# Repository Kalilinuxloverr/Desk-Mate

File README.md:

# Desk-Mate

Ein kleiner Wall-E-artiger Schreibtisch-Begleiter: eine Ampel für alles, was dich braucht (Claude Code, Browser-Downloads, Steam), ein Deck mit Motorfadern und Soft-Keys, ein Kopf mit zwei Augen-Displays. Verbunden per USB, BLE und WiFi; steuerbar vom Mac, vom Handy und über das Haus-MQTT. Alles Through-Hole, alles 3D-gedruckt, alles dokumentiert — inklusive Arbeitszeit.

**Zwischenstand (2026-10-09):**

| Schritt | Stand |
|---|---|
| Design-Spec (18 Grill-Fragen) | ✅ [`docs/superpowers/specs/`](docs/superpowers/specs/2026-08-22-desk-mate-design.md) |
| Pin-Map gegen Datenblatt + DevKit-Schaltplan verifiziert | ✅ [`firmware/arduino/deskmate/pins.h`](firmware/arduino/deskmate/pins.h) |
| Stückliste mit Quellen und Preisen, Teile bestellt (Amazon ~142 €) | ✅ [`hardware/bom.md`](hardware/bom.md) |
| KiCad final: Mainboard 100×100 · Frontpanel 120×136 · Augen-Adapter 42×30 — nur THT, Teile von Reichelt, Silkscreen mit Logo und Pin-Namen, ERC/DRC sauber, Gerber exportiert | ✅ [`hardware/kicad/`](hardware/kicad/README.md) |
| Bestellung Reichelt + JLCPCB | 🔜 bereit — Gerber in `hardware/kicad/<board>/fab/`, Liste in [`vault/Bestellungen/2026-10-09-reichelt.md`](vault/Bestellungen/2026-10-09-reichelt.md) |
| Firmware · Agent/App · Gehäuse | ⬜ danach |

Arbeitszeit und Tagesprotokolle: [`vault/Log/`](vault/Log/) · Projektseite: Portfolio-Eintrag P12.

```
 ┌─────────────────────┐
 │ KOPF  (pan/tilt)    │  Augen-Adapter-PCB → 2× GC9A01 (rund, 1,28")
 │                     │  WS2812-Ring (Ampel) · 2× MG90S im Hals
 ├─────────────────────┤
 │ BAUCH / DECK        │  FRONTPANEL-PCB
 │  [ 2,8" ILI9341 ]   │   6 Soft-Keys unter dem Display
 │  [k][k][k][k][k][k] │   4 Makro-Keys · EC11-Encoder
 │  |F| [k][k] (o) |F| │   2(4)× X32-Motorfader · MCP23017 · MPR121
 │  |F|  [k][k]    |F| │
 ├─────────────────────┤
 │ BASE (statisch)     │  MAINBOARD-PCB
 │  USB-C(D) USB-C(P)  │   ESP32-S3 DevKitC-1 · 2× USB-C · LD1117V33
 │  BME680             │   2(4)× DRV8833 · VM-Boost optional
 └─────────────────────┘
          │ USB / BLE / WiFi-MQTT
   ┌──────┴──────┐      ┌──────────┐      ┌────────────┐
   │ macOS-Agent │◄────►│ iOS-App  │      │ Claude Code│──Hooks──► Agent
   │ (Menüleiste)│ MQTT │          │      └────────────┘
   └─────────────┘      └──────────┘
```

| Pfad | Inhalt |
|---|---|
| `docs/superpowers/specs/` | Design-Spec (die eine Wahrheit für Hardware, Pin-Map, Protokolle) |
| `docs/superpowers/plans/` | Implementierungspläne je Phase |
| `docs/relic/` | Der Ursprungs-Prompt, unverändert |
| [`docs/anleitung/`](docs/anleitung/) | Bauanleitung (wächst mit dem Projekt) |
| `docs/logo/` | Logo (SVG) |
| `vault/` | Obsidian-Vault: Tagesblätter mit Arbeitszeit, Entscheidungen, Bestellungen |
| `hardware/kicad/` | Mainboard, Frontpanel, Augen-Adapter (KiCad 10) |
| `hardware/3d/` | Gehäuse (STEP + STL) |
| `hardware/bom.md` | Stückliste |
| `firmware/arduino/deskmate/` | ESP32-S3-Firmware (arduino-cli) |
| `app/` | macOS-Agent + iOS-App (Swift, XcodeGen) |
| `agent-windows/` | Windows-Tray (Python, Phase 2) |
| `server/` | Vercel-Function für Push |
| `tools/` | Session-Hooks, Secret-Check |

## Hardware

| Mainboard (Base) | Frontpanel (Deck) | Augen-Adapter |
|---|---|---|
|  |  |  |

Drei Through-Hole-Platinen, alle Module gesteckt (ESP32-S3-DevKitC-1, Pololu DRV8833, MPR121, Displays). Schaltpläne als PDF, STEP-Modelle und JLCPCB-Gerber-Zips liegen in `hardware/kicad/<board>/fab/`; Aufbau und Entwurfsregeln in [`hardware/kicad/README.md`](hardware/kicad/README.md), Bestellanleitung in [`docs/anleitung/01-platinen.md`](docs/anleitung/01-platinen.md).

## Bauen

Nach dem Klonen einmalig:

```bash
git config core.hooksPath tools/githooks   # Secret-Check vor jedem Commit
sh tools/test-check-secrets.sh             # muss "OK" sagen
sh tools/test-session-hooks.sh             # muss "OK" sagen
sh tools/test-pins.sh                      # Pin-Map-Regeln
sh tools/test-kicad.sh                     # ERC + DRC + Netzliste (braucht KiCad 10 unter /Applications)
```

KiCad-Dateien neu erzeugen/exportieren: siehe [`hardware/kicad/README.md`](hardware/kicad/README.md). Firmware- und App-Befehle kommen mit den jeweiligen Phasen dazu (siehe `CLAUDE.md`).

## Lizenz

MIT (Code). Lizenz für die Hardware-Dateien wird noch festgelegt.

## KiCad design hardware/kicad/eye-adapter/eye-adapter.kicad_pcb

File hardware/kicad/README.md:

# KiCad — drei Platinen, eine JLCPCB-Bestellung

| Ordner | Platine | Maß | Inhalt |
|---|---|---|---|
| `mainboard/` | Base | 100 × 100 mm | S3-DevKit-Sockel, Schraubklemme für das USB-C-Breakout (5 V/3 A), Polyfuse + SB540, LD1117V33, 2× DRV8833-Sockel, Servo/ARGB/I²C-Stiftleisten, Augen-Kabel IDC 2×5, IDC 2×15, MT3608-Header (VM-Boost, optional) |
| `frontpanel/` | Deck | 120 × 136 mm | 10× MX, EC11, MCP23017, MPR121-Stiftleiste (Modul per Kabel), ILI9341-Sockel + 4 Abstandshalter, 4× Fader-Header, Backlight-Schalter, IDC 2×15 |
| `eye-adapter/` | Kopf | 42 × 30 mm | IDC 2×5 ein, 2× 1×7-Stiftleiste für die GC9A01 (per Dupont-Kabel) |
| `lib/` | — | — | Projektbibliothek `deskmate.kicad_sym` + `deskmate.pretty` (Modul-Sockel, Polyfuse) |
| `gen/` | — | — | Generator (siehe unten) |
| `<board>/fab/` | — | — | Gerber/Drill-Zip, STEP, Render — das geht zu JLCPCB |

Regeln (JLCPCB 2-Lagen): Leiterbahn ≥ 0,2 mm, Abstand ≥ 0,127 mm, Via 0,8/0,4 mm, Rand 0,3 mm. Netzklassen (Breite / Abstand 0,13): Default 0,25, Power 1,0 (Mainboard) bzw. 0,8 (Frontpanel), Motor 0,6, Power3V3 0,6 — Werte stehen in `gen/boards.py` und `gen/build_sch.py`. Massefläche beidseitig, Sperrzone unter der DevKit-Antenne.

## Generator statt Handarbeit (Erstversion)

Die Erstversion aller Dateien wurde aus `gen/boards.py` erzeugt — eine Tabelle „Bauteil → Pin → Netz → Position“. So sind Schaltplan, Layout und `netlist.json` per Konstruktion identisch, und `tools/test-kicad.sh` prüft das gegen KiCads eigene Netzliste.

```bash
cd hardware/kicad/gen
python3 build_sch.py                       # Bibliothek, Schaltpläne, Projekte, netlist.json
KIPY=/Applications/KiCad/KiCad.app/Contents/Frameworks/Python.framework/Versions/3.9/bin/python3
$KIPY build_pcb.py mainboard --force       # Layout platzieren, Freerouting, Zonen füllen
$KIPY export_fab.py mainboard              # Gerber/Drill/STEP/Render nach mainboard/fab/
sh ../../../tools/test-kicad.sh            # ERC + DRC + Netzlisten-Abgleich
```

`build_pcb.py` routet bis zu 6-mal mit wechselnder Strategie und behält den ersten Lauf mit 0 offenen Verbindungen; GND-Pads sind vollflächig an die Massefläche angebunden (beim Löten heißer/länger). Freerouting: `~/Applications/freerouting-2.3.0.jar` (Java 17+; `curl -L -o ~/Applications/freerouting-2.3.0.jar https://github.com/freerouting/freerouting/releases/download/v2.3.0/freerouting-2.3.0.jar`).

**Wichtig:** Sobald in der KiCad-GUI etwas geändert wurde, sind die `.kicad_sch`/`.kicad_pcb` die Wahrheit — `build_*.py` nicht mehr blind laufen lassen (`build_pcb.py` weigert sich ohne `--force`). Der Generator ist ein Bootstrap, kein Roundtrip.

Der Schaltplan ist „Label-Stil“: jedes Pin trägt ein globales Label, keine Leitungen. Elektrisch vollständig, optisch schlicht — in der GUI beliebig umsortierbar.

## Was vor der Bestellung am echten Teil zu prüfen ist

Siehe `vault/Hardware/Module-Masse.md` (Quellen + Konfidenz). Kurz: DevKit-Reihenabstand 22,86 (hoch), Pololu-Raster 10,16 (hoch), MPR121-Clone 17,78 (mittel — nachmessen), ILI9341 MSP2807-Löcher (hoch), X32-Fader-Pins (unbekannt — Drähte an Stiftleiste).

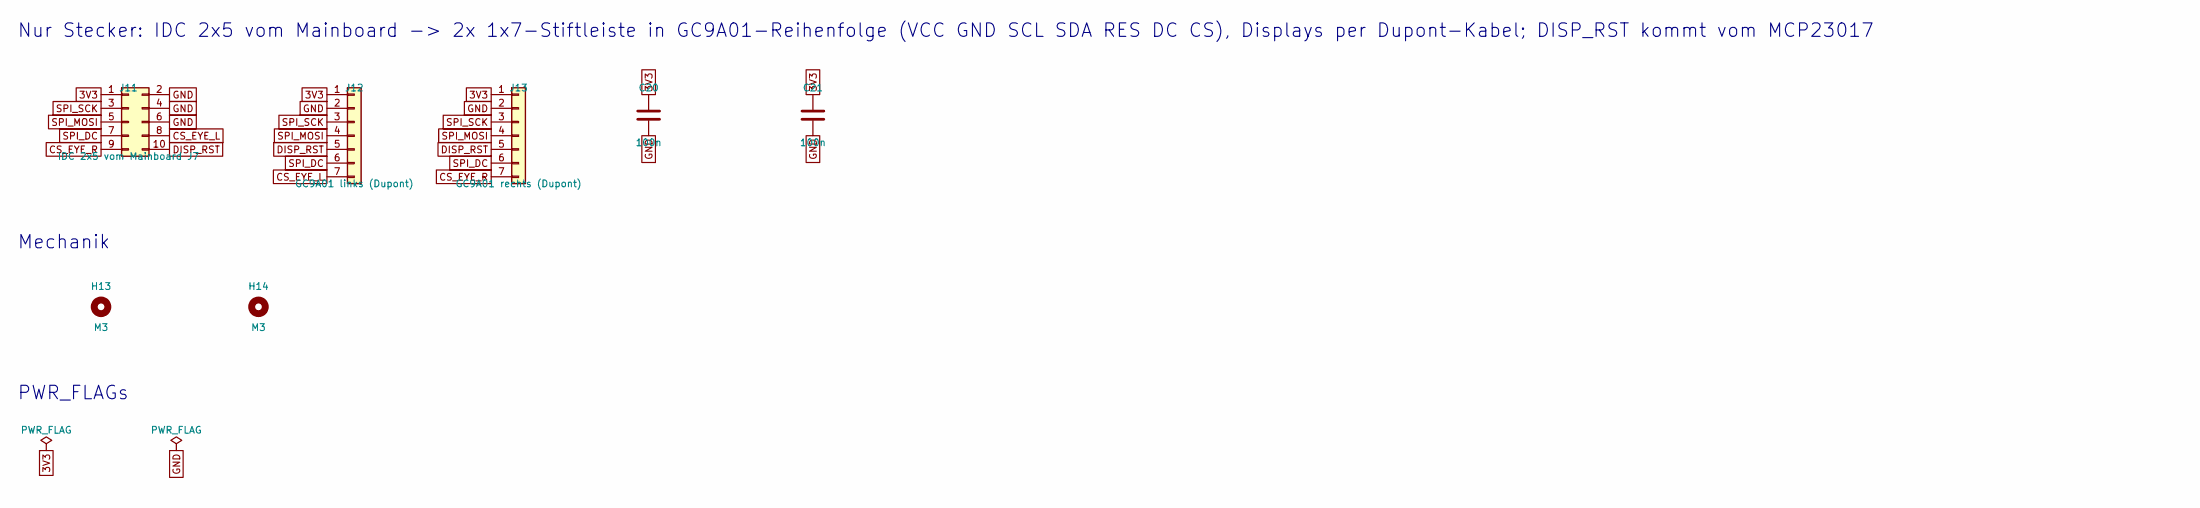
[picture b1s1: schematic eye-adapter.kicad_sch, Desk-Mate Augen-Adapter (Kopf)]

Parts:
C20, C21: 100n; C_Disc_D5.0mm_W2.5mm_P5.00mm
H13, H14: M3; MountingHole_3.2mm_M3
J11: IDC 2x5 vom Mainboard J7; IDC-Header_2x05_P2.54mm_Vertical
J12: GC9A01 links (Dupont); PinHeader_1x07_P2.54mm_Vertical
J13: GC9A01 rechts (Dupont); PinHeader_1x07_P2.54mm_Vertical

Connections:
3V3: C20.1, C21.1, J11.1, J12.1, J13.1
CS_EYE_L: J11.8, J12.7
CS_EYE_R: J11.9, J13.7
DISP_RST: J11.10, J12.5, J13.5
GND: C20.2, C21.2, J11.2, J11.4, J11.6, J12.2, J13.2
SPI_DC: J11.7, J12.6, J13.6
SPI_MOSI: J11.5, J12.4, J13.4
SPI_SCK: J11.3, J12.3, J13.3

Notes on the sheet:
Nur Stecker: IDC 2x5 vom Mainboard -> 2x 1x7-Stiftleiste in GC9A01-Reihenfolge (VCC GND SCL SDA RES DC CS), Displays per Dupont-Kabel; DISP_RST kommt vom MCP23017
Mechanik
PWR_FLAGs

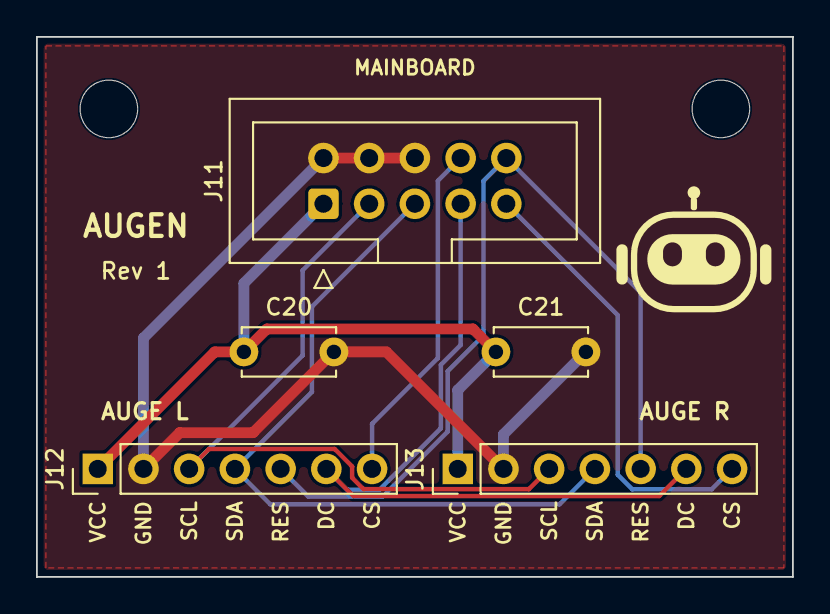
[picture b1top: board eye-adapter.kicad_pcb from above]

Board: 2 copper layers, 42.0 x 30.0 mm, 7 parts (0 on the bottom side), 8 nets.

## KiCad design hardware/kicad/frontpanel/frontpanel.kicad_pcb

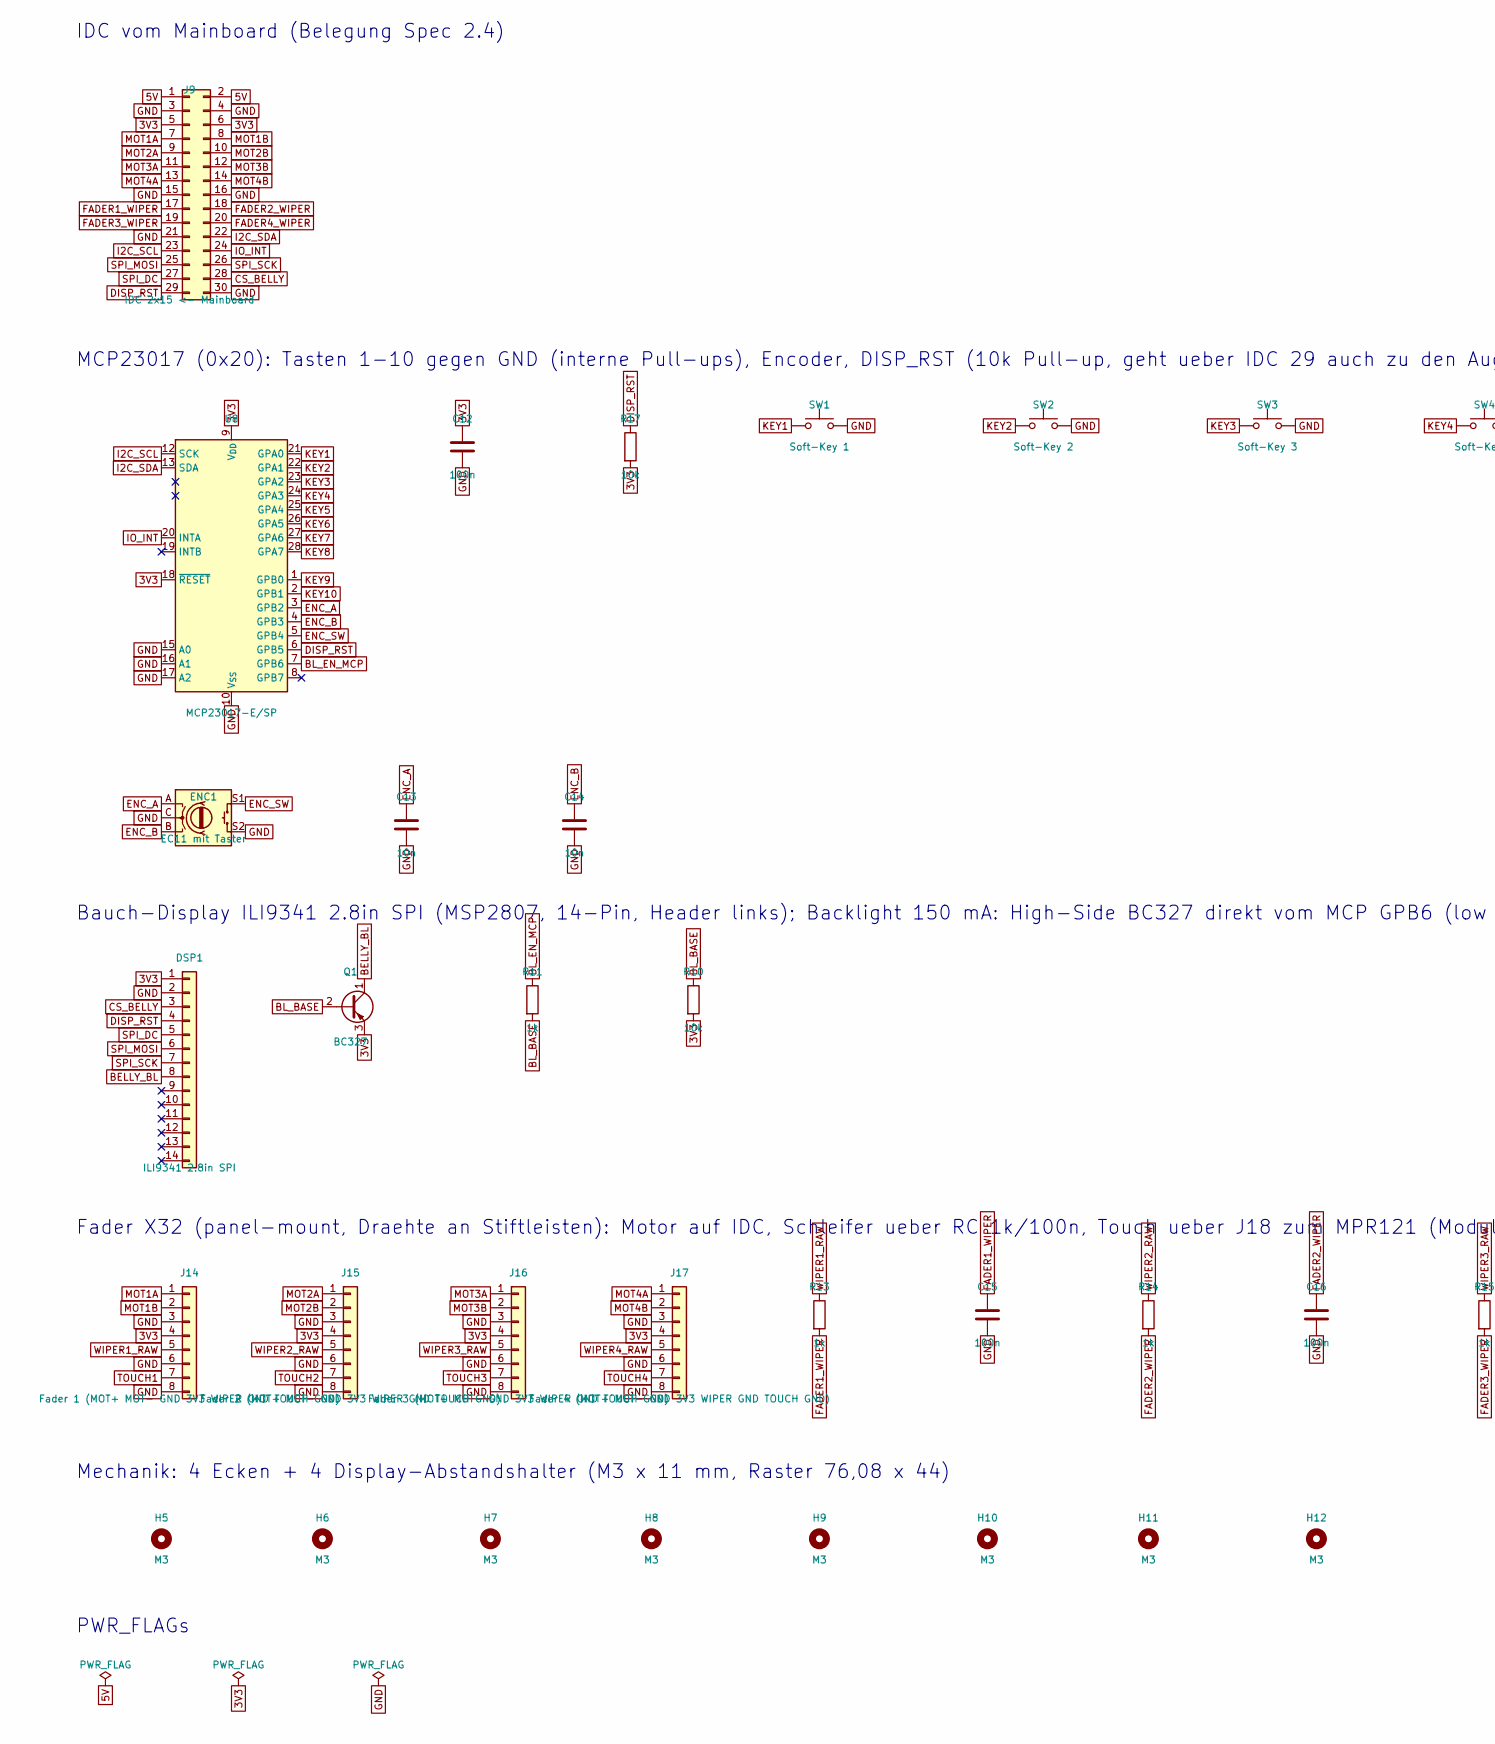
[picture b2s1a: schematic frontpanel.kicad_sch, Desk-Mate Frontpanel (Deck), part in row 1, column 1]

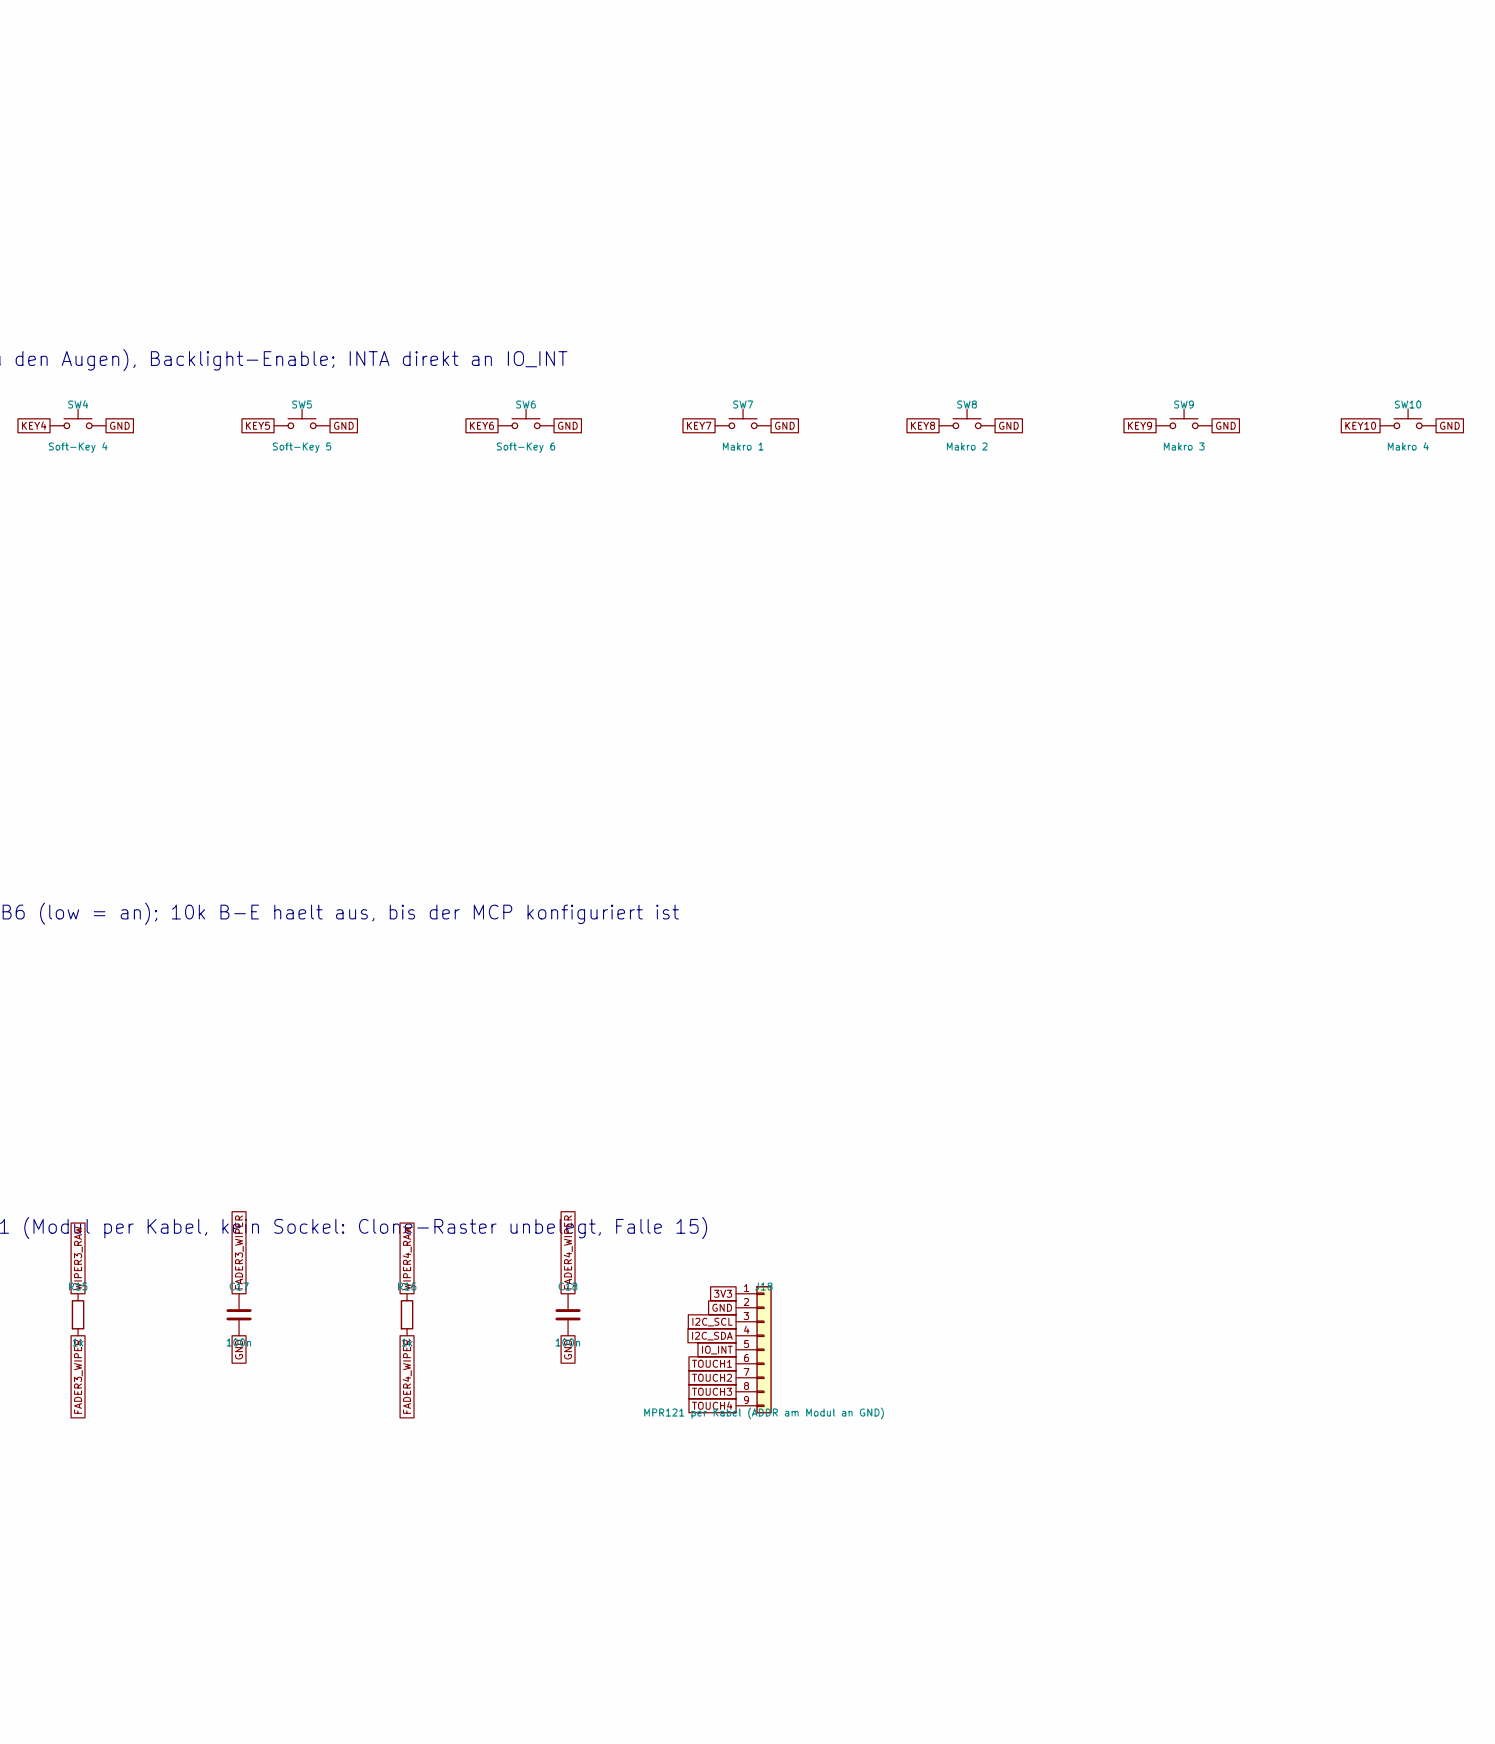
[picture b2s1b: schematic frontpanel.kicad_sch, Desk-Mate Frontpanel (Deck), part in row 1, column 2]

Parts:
C12, C15, C16, C17, C18: 100n; C_Disc_D5.0mm_W2.5mm_P5.00mm
C13, C14: 10n; C_Disc_D5.0mm_W2.5mm_P5.00mm
DSP1: ILI9341 2.8in SPI; PinSocket_1x14_P2.54mm_Vertical
ENC1: EC11 mit Taster; RotaryEncoder_Alps_EC11E-Switch_Vertical_H20mm
H5, H6, H7, H8, H9, H10, H11, H12: M3; MountingHole_3.2mm_M3
J9: IDC 2x15 <- Mainboard; IDC-Header_2x15_P2.54mm_Vertical
J14: Fader 1 (MOT+ MOT- GND 3V3 WIPER GND TOUCH GND); PinHeader_1x08_P2.54mm_Vertical
J15: Fader 2 (MOT+ MOT- GND 3V3 WIPER GND TOUCH GND); PinHeader_1x08_P2.54mm_Vertical
J16: Fader 3 (MOT+ MOT- GND 3V3 WIPER GND TOUCH GND); PinHeader_1x08_P2.54mm_Vertical
J17: Fader 4 (MOT+ MOT- GND 3V3 WIPER GND TOUCH GND); PinHeader_1x08_P2.54mm_Vertical
J18: MPR121 per Kabel (ADDR am Modul an GND); PinHeader_1x09_P2.54mm_Vertical
Q1: BC327; TO-92_Inline
R10, R17: 10k; R_Axial_DIN0207_L6.3mm_D2.5mm_P10.16mm_Horizontal
R11, R13, R14, R15, R16: 1k; R_Axial_DIN0207_L6.3mm_D2.5mm_P10.16mm_Horizontal
SW1: Soft-Key 1; SW_Cherry_MX_1.00u_PCB
SW2: Soft-Key 2; SW_Cherry_MX_1.00u_PCB
SW3: Soft-Key 3; SW_Cherry_MX_1.00u_PCB
SW4: Soft-Key 4; SW_Cherry_MX_1.00u_PCB
SW5: Soft-Key 5; SW_Cherry_MX_1.00u_PCB
SW6: Soft-Key 6; SW_Cherry_MX_1.00u_PCB
SW7: Makro 1; SW_Cherry_MX_1.00u_PCB
SW8: Makro 2; SW_Cherry_MX_1.00u_PCB
SW9: Makro 3; SW_Cherry_MX_1.00u_PCB
SW10: Makro 4; SW_Cherry_MX_1.00u_PCB
U8: MCP23017-E/SP; DIP-28_W7.62mm_Socket

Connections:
3V3: C12.1, DSP1.1, J9.5, J9.6, J14.4, J15.4, J16.4, J17.4, J18.1, Q1.3 (E), R10.2, R17.2, U8.9 (V_{DD}), U8.18 (~RESET)
5V: J9.1, J9.2
BELLY_BL: DSP1.8, Q1.1 (C)
BL_BASE: Q1.2 (B), R10.1, R11.2
BL_EN_MCP: R11.1, U8.7 (GPB6)
CS_BELLY: DSP1.3, J9.28
DISP_RST: DSP1.4, J9.29, R17.1, U8.6 (GPB5)
ENC_A: C13.1, ENC1.A, U8.3 (GPB2)
ENC_B: C14.1, ENC1.B, U8.4 (GPB3)
ENC_SW: ENC1.S1, U8.5 (GPB4)
FADER1_WIPER: C15.1, J9.17, R13.2
FADER2_WIPER: C16.1, J9.18, R14.2
FADER3_WIPER: C17.1, J9.19, R15.2
FADER4_WIPER: C18.1, J9.20, R16.2
GND: C12.2, C13.2, C14.2, C15.2, C16.2, C17.2, C18.2, DSP1.2, ENC1.C, ENC1.S2, J9.3, J9.4, J9.15, J9.16, J9.21, J9.30, J14.3, J14.6, J14.8, J15.3, J15.6, J15.8, J16.3, J16.6, J16.8, J17.3, J17.6, J17.8, J18.2, SW1.2, SW2.2, SW3.2, SW4.2, SW5.2, SW6.2, SW7.2, SW8.2, SW9.2, SW10.2, U8.10 (V_{SS}), U8.15 (A0), U8.16 (A1), U8.17 (A2)
I2C_SCL: J9.23, J18.3, U8.12 (SCK)
I2C_SDA: J9.22, J18.4, U8.13 (SDA)
IO_INT: J9.24, J18.5, U8.20 (INTA)
KEY1: SW1.1, U8.21 (GPA0)
KEY2: SW2.1, U8.22 (GPA1)
KEY3: SW3.1, U8.23 (GPA2)
KEY4: SW4.1, U8.24 (GPA3)
KEY5: SW5.1, U8.25 (GPA4)
KEY6: SW6.1, U8.26 (GPA5)
KEY7: SW7.1, U8.27 (GPA6)
KEY8: SW8.1, U8.28 (GPA7)
KEY9: SW9.1, U8.1 (GPB0)
KEY10: SW10.1, U8.2 (GPB1)
MOT1A: J9.7, J14.1
MOT1B: J9.8, J14.2
MOT2A: J9.9, J15.1
MOT2B: J9.10, J15.2
MOT3A: J9.11, J16.1
MOT3B: J9.12, J16.2
MOT4A: J9.13, J17.1
MOT4B: J9.14, J17.2
SPI_DC: DSP1.5, J9.27
SPI_MOSI: DSP1.6, J9.25
SPI_SCK: DSP1.7, J9.26
TOUCH1: J14.7, J18.6
TOUCH2: J15.7, J18.7
TOUCH3: J16.7, J18.8
TOUCH4: J17.7, J18.9
WIPER1_RAW: J14.5, R13.1
WIPER2_RAW: J15.5, R14.1
WIPER3_RAW: J16.5, R15.1
WIPER4_RAW: J17.5, R16.1

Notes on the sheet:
IDC vom Mainboard (Belegung Spec 2.4)
MCP23017 (0x20): Tasten 1-10 gegen GND (interne Pull-ups), Encoder, DISP_RST (10k Pull-up, geht ueber IDC 29 auch zu den Augen), Backlight-Enable; INTA direkt an IO_INT
Bauch-Display ILI9341 2.8in SPI (MSP2807, 14-Pin, Header links); Backlight 150 mA: High-Side BC327 direkt vom MCP GPB6 (low = an); 10k B-E haelt aus, bis der MCP konfiguriert ist
Fader X32 (panel-mount, Draehte an Stiftleisten): Motor auf IDC, Schleifer ueber RC 1k/100n, Touch ueber J18 zum MPR121 (Modul per Kabel, kein Sockel: Clone-Raster unbelegt, Falle 15)
Mechanik: 4 Ecken + 4 Display-Abstandshalter (M3 x 11 mm, Raster 76,08 x 44)
PWR_FLAGs

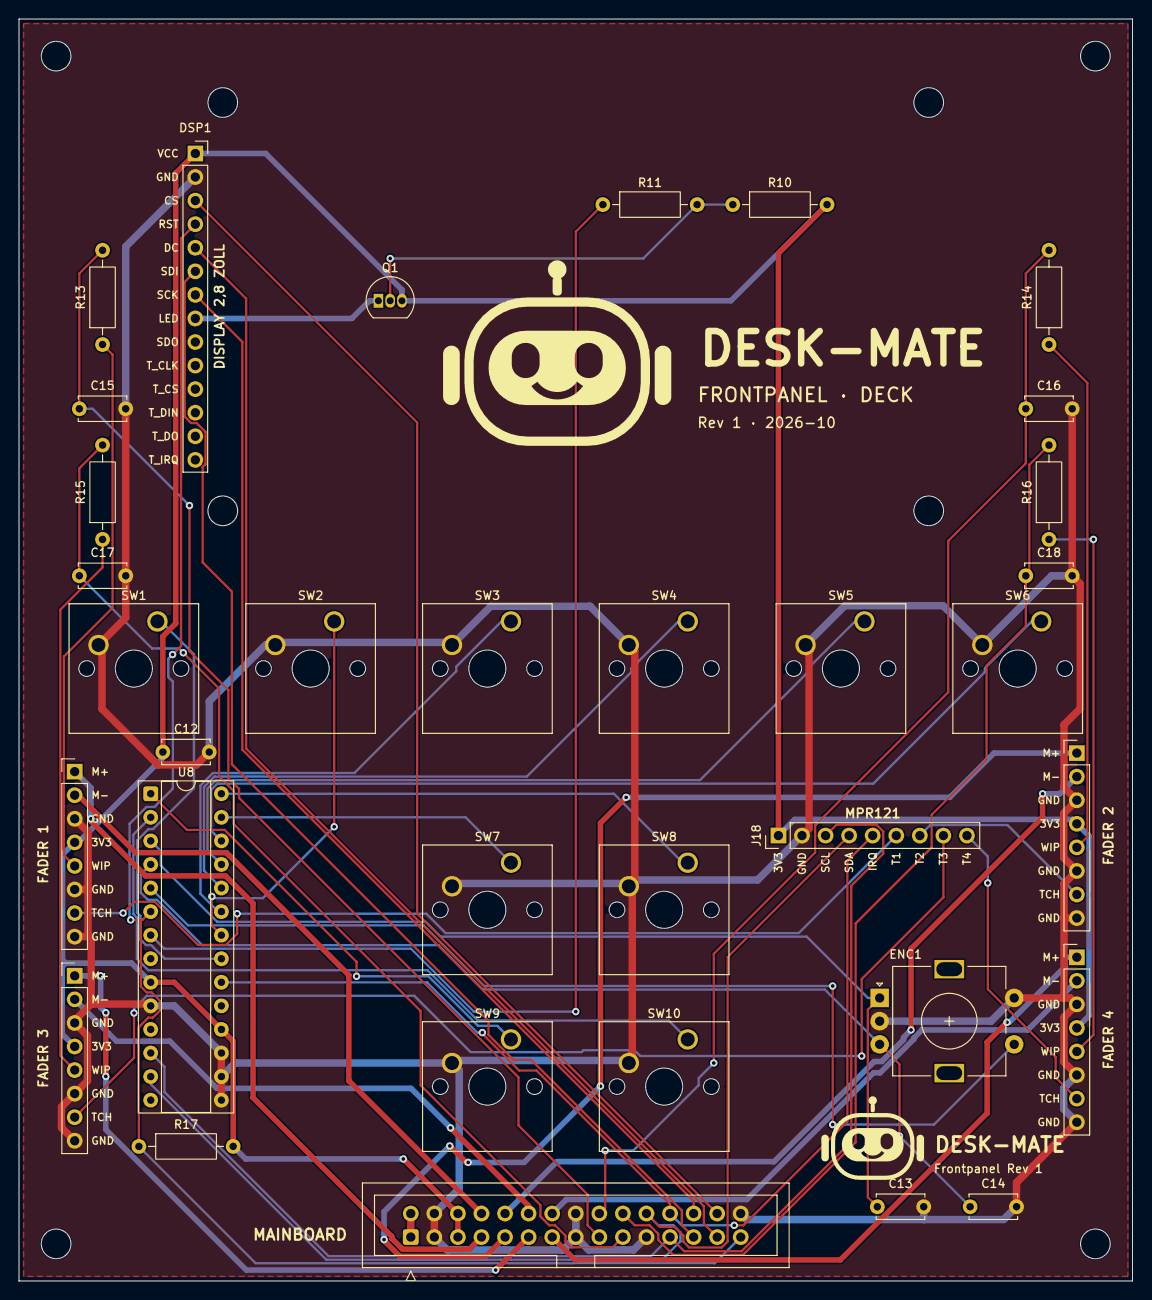
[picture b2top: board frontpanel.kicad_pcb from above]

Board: 2 copper layers, 120.0 x 136.0 mm, 42 parts (0 on the bottom side), 47 nets.

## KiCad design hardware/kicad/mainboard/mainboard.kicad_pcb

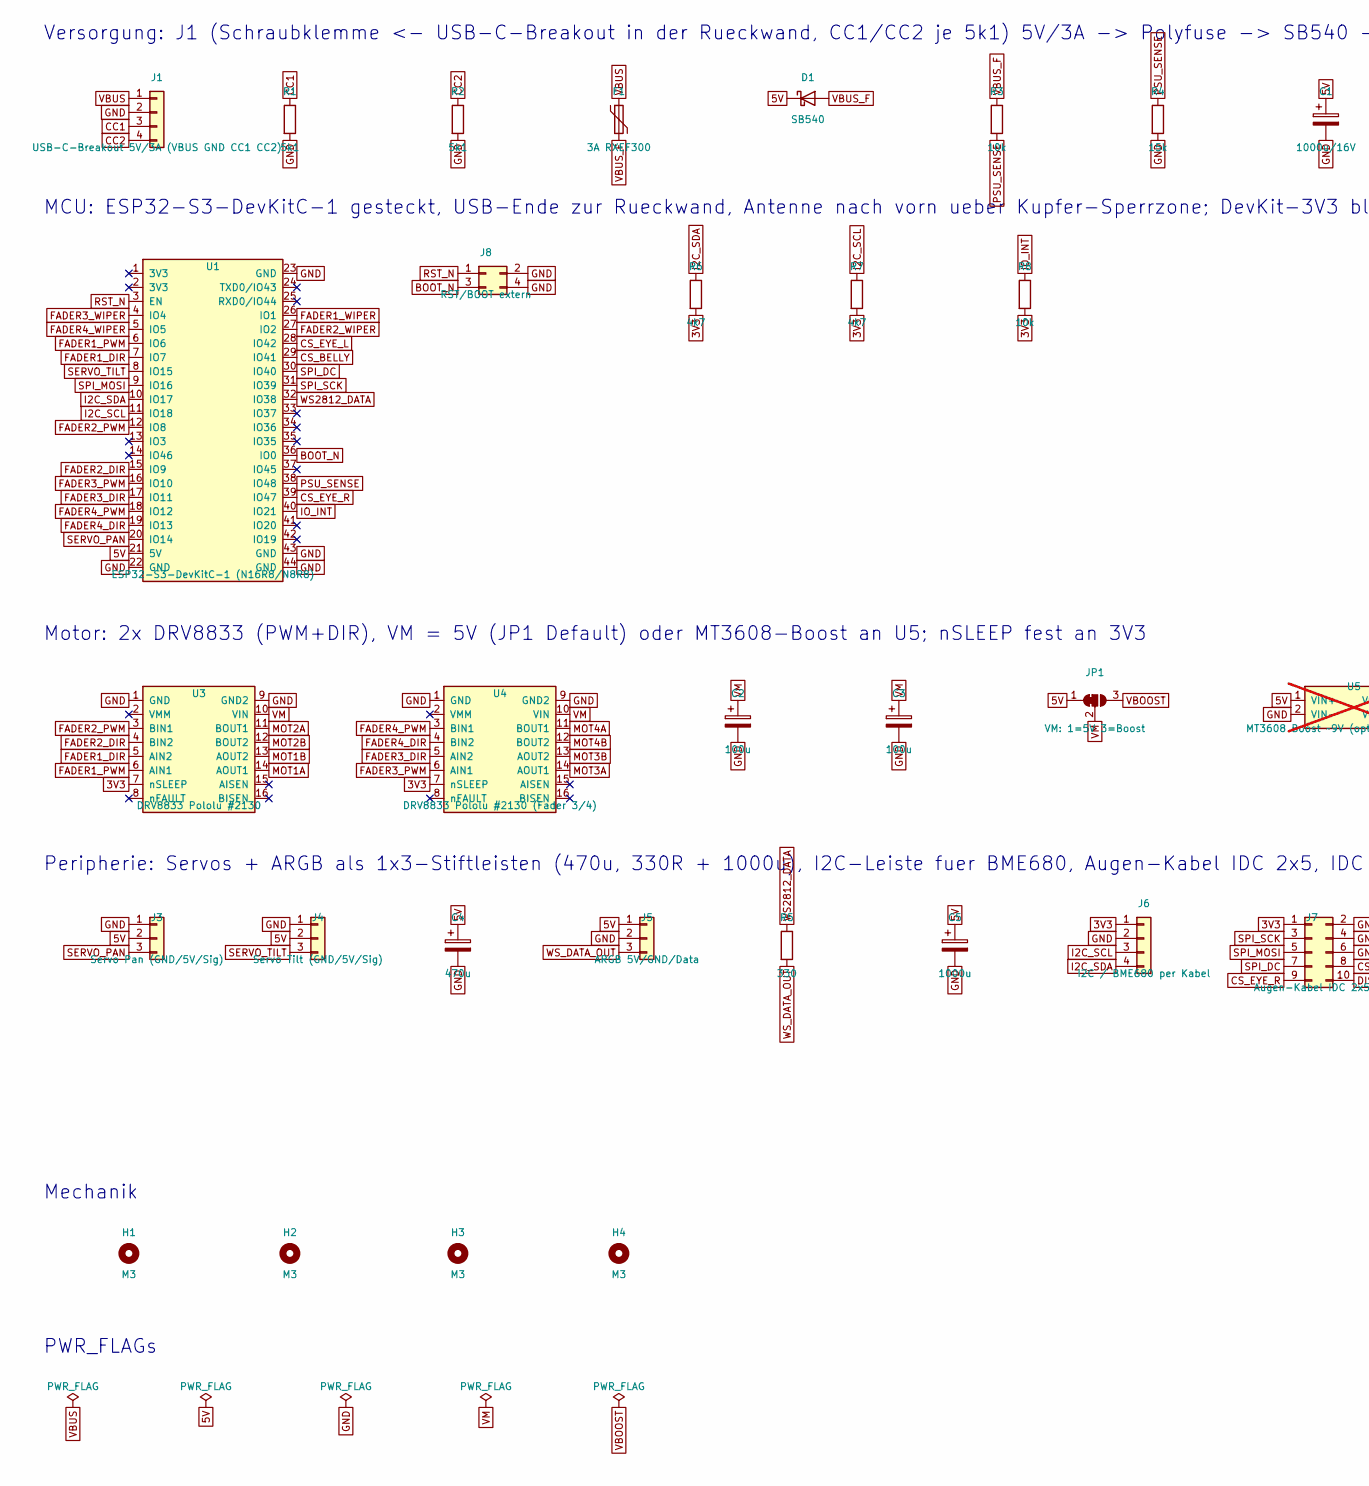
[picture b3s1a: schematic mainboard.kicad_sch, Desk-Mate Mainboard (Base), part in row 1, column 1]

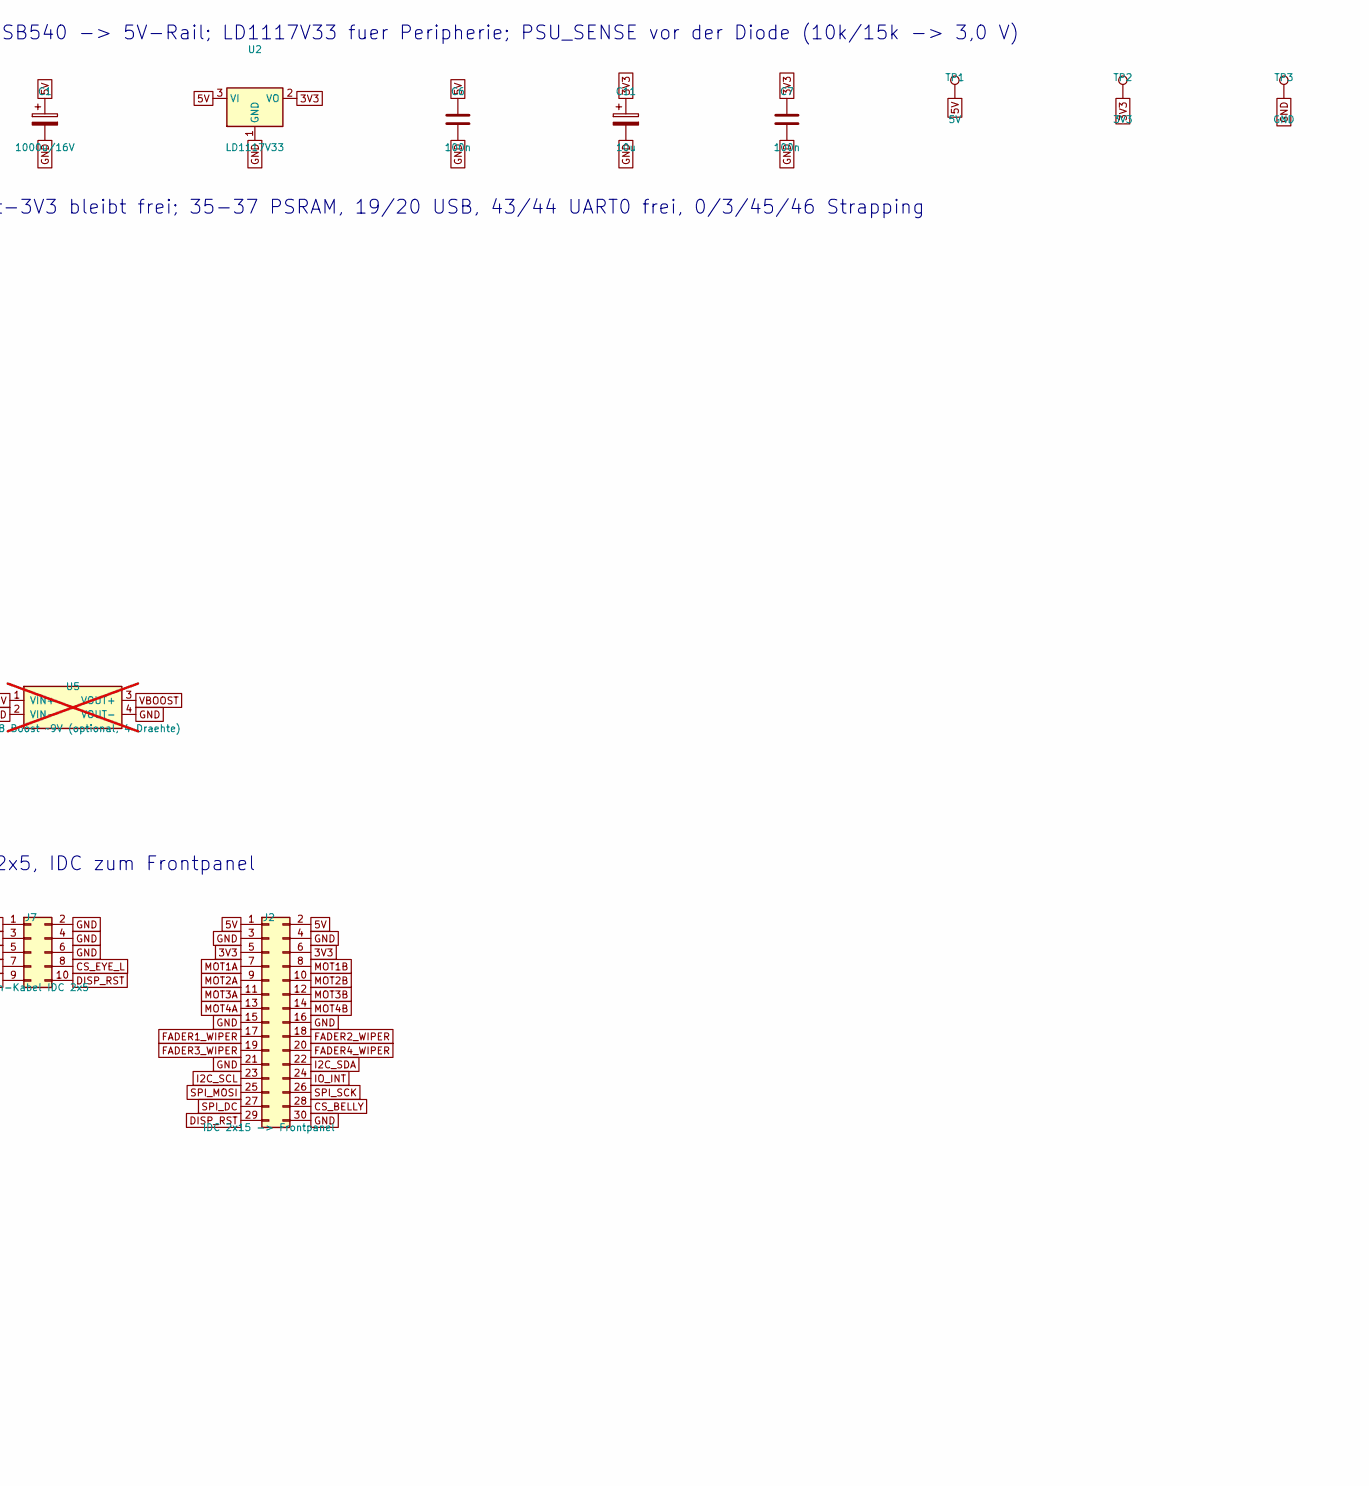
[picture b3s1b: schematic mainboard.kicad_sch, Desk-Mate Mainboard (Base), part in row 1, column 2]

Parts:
C1: 1000u/16V; CP_Radial_D10.0mm_P5.00mm
C2, C3: 100u; CP_Radial_D6.3mm_P2.50mm
C4: 470u; CP_Radial_D8.0mm_P3.50mm
C5: 1000u; CP_Radial_D10.0mm_P5.00mm
C6, C7: 100n; C_Disc_D5.0mm_W2.5mm_P5.00mm
C11: 10u; CP_Radial_D5.0mm_P2.00mm
D1: SB540; D_DO-201_P15.24mm_Horizontal
F1: 3A RXEF300; Polyfuse_Radial_P5.08mm
H1, H2, H3, H4: M3; MountingHole_3.2mm_M3
J1: USB-C-Breakout 5V/3A (VBUS GND CC1 CC2); TerminalBlock_Phoenix_MKDS-1,5-4-5.08_1x04_P5.08mm_Horizont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
J2: IDC 2x15 -> Frontpanel; IDC-Header_2x15_P2.54mm_Vertical
J3: Servo Pan (GND/5V/Sig); PinHeader_1x03_P2.54mm_Vertical
J4: Servo Tilt (GND/5V/Sig); PinHeader_1x03_P2.54mm_Vertical
J5: ARGB 5V/GND/Data; PinHeader_1x03_P2.54mm_Vertical
J6: I2C / BME680 per Kabel; PinHeader_1x04_P2.54mm_Vertical
J7: Augen-Kabel IDC 2x5; IDC-Header_2x05_P2.54mm_Vertical
J8: RST/BOOT extern; PinHeader_2x02_P2.54mm_Vertical
JP1: VM: 1=5V 3=Boost; SolderJumper-3_P1.3mm_Bridged12_RoundedPad1.0x1.5mm_NumberL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
R1, R2: 5k1; R_Axial_DIN0207_L6.3mm_D2.5mm_P10.16mm_Horizontal
R3, R8: 10k; R_Axial_DIN0207_L6.3mm_D2.5mm_P10.16mm_Horizontal
R4: 15k; R_Axial_DIN0207_L6.3mm_D2.5mm_P10.16mm_Horizontal
R5: 330; R_Axial_DIN0207_L6.3mm_D2.5mm_P10.16mm_Horizontal
R6, R7: 4k7; R_Axial_DIN0207_L6.3mm_D2.5mm_P10.16mm_Horizontal
TP1: 5V; TestPoint_THTPad_1.5x1.5mm_Drill0.7mm
TP2: 3V3; TestPoint_THTPad_1.5x1.5mm_Drill0.7mm
TP3: GND; TestPoint_THTPad_1.5x1.5mm_Drill0.7mm
U1: ESP32-S3-DevKitC-1 (N16R8/N8R8); ESP32-S3-DevKitC-1_Socket
U2: LD1117V33; TO-220-3_Vertical
U3: DRV8833 Pololu #2130; DRV8833_Socket
U4: DRV8833 Pololu #2130 (Fader 3/4); DRV8833_Socket
U5: MT3608 Boost ~9V (optional, 4 Draehte); PinHeader_1x04_P2.54mm_Vertical; not fitted

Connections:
3V3: C7.1, C11.1, J2.5, J2.6, J6.1, J7.1, R6.2, R7.2, R8.2, TP2.1, U2.2 (VO), U3.7 (nSLEEP), U4.7 (nSLEEP)
5V: C1.1, C4.1, C5.1, C6.1, D1.1 (K), J2.1, J2.2, J3.2, J4.2, J5.1, JP1.1 (A), TP1.1, U1.21 (5V), U2.3 (VI), U5.1 (VIN+)
BOOT_N: J8.3, U1.36 (IO0)
CC1: J1.3, R1.1
CC2: J1.4, R2.1
CS_BELLY: J2.28, U1.29 (IO41)
CS_EYE_L: J7.8, U1.28 (IO42)
CS_EYE_R: J7.9, U1.39 (IO47)
DISP_RST: J2.29, J7.10
FADER1_DIR: U1.7 (IO7), U3.5 (AIN2)
FADER1_PWM: U1.6 (IO6), U3.6 (AIN1)
FADER1_WIPER: J2.17, U1.26 (IO1)
FADER2_DIR: U1.15 (IO9), U3.4 (BIN2)
FADER2_PWM: U1.12 (IO8), U3.3 (BIN1)
FADER2_WIPER: J2.18, U1.27 (IO2)
FADER3_DIR: U1.17 (IO11), U4.5 (AIN2)
FADER3_PWM: U1.16 (IO10), U4.6 (AIN1)
FADER3_WIPER: J2.19, U1.4 (IO4)
FADER4_DIR: U1.19 (IO13), U4.4 (BIN2)
FADER4_PWM: U1.18 (IO12), U4.3 (BIN1)
FADER4_WIPER: J2.20, U1.5 (IO5)
GND: C1.2, C2.2, C3.2, C4.2, C5.2, C6.2, C7.2, C11.2, J1.2, J2.3, J2.4, J2.15, J2.16, J2.21, J2.30, J3.1, J4.1, J5.2, J6.2, J7.2, J7.4, J7.6, J8.2, J8.4, R1.2, R2.2, R4.2, TP3.1, U1.22 (GND), U1.23 (GND), U1.43 (GND), U1.44 (GND), U2.1 (GND), U3.1 (GND), U3.9 (GND2), U4.1 (GND), U4.9 (GND2), U5.2 (VIN-), U5.4 (VOUT-)
I2C_SCL: J2.23, J6.3, R7.1, U1.11 (IO18)
I2C_SDA: J2.22, J6.4, R6.1, U1.10 (IO17)
IO_INT: J2.24, R8.1, U1.40 (IO21)
MOT1A: J2.7, U3.14 (AOUT1)
MOT1B: J2.8, U3.13 (AOUT2)
MOT2A: J2.9, U3.11 (BOUT1)
MOT2B: J2.10, U3.12 (BOUT2)
MOT3A: J2.11, U4.14 (AOUT1)
MOT3B: J2.12, U4.13 (AOUT2)
MOT4A: J2.13, U4.11 (BOUT1)
MOT4B: J2.14, U4.12 (BOUT2)
PSU_SENSE: R3.2, R4.1, U1.38 (IO48)
RST_N: J8.1, U1.3 (EN)
SERVO_PAN: J3.3, U1.20 (IO14)
SERVO_TILT: J4.3, U1.8 (IO15)
SPI_DC: J2.27, J7.7, U1.30 (IO40)
SPI_MOSI: J2.25, J7.5, U1.9 (IO16)
SPI_SCK: J2.26, J7.3, U1.31 (IO39)
VBOOST: JP1.3 (B), U5.3 (VOUT+)
VBUS: F1.1, J1.1
VBUS_F: D1.2 (A), F1.2, R3.1
VM: C2.1, C3.1, JP1.2 (C), U3.10 (VIN), U4.10 (VIN)
WS2812_DATA: R5.1, U1.32 (IO38)
WS_DATA_OUT: J5.3, R5.2

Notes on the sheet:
Versorgung: J1 (Schraubklemme <- USB-C-Breakout in der Rueckwand, CC1/CC2 je 5k1) 5V/3A -> Polyfuse -> SB540 -> 5V-Rail; LD1117V33 fuer Peripherie; PSU_SENSE vor der Diode (10k/15k -> 3,0 V)
MCU: ESP32-S3-DevKitC-1 gesteckt, USB-Ende zur Rueckwand, Antenne nach vorn ueber Kupfer-Sperrzone; DevKit-3V3 bleibt frei; 35-37 PSRAM, 19/20 USB, 43/44 UART0 frei, 0/3/45/46 Strapping
Motor: 2x DRV8833 (PWM+DIR), VM = 5V (JP1 Default) oder MT3608-Boost an U5; nSLEEP fest an 3V3
Peripherie: Servos + ARGB als 1x3-Stiftleisten (470u, 330R + 1000u), I2C-Leiste fuer BME680, Augen-Kabel IDC 2x5, IDC zum Frontpanel
Mechanik
PWR_FLAGs

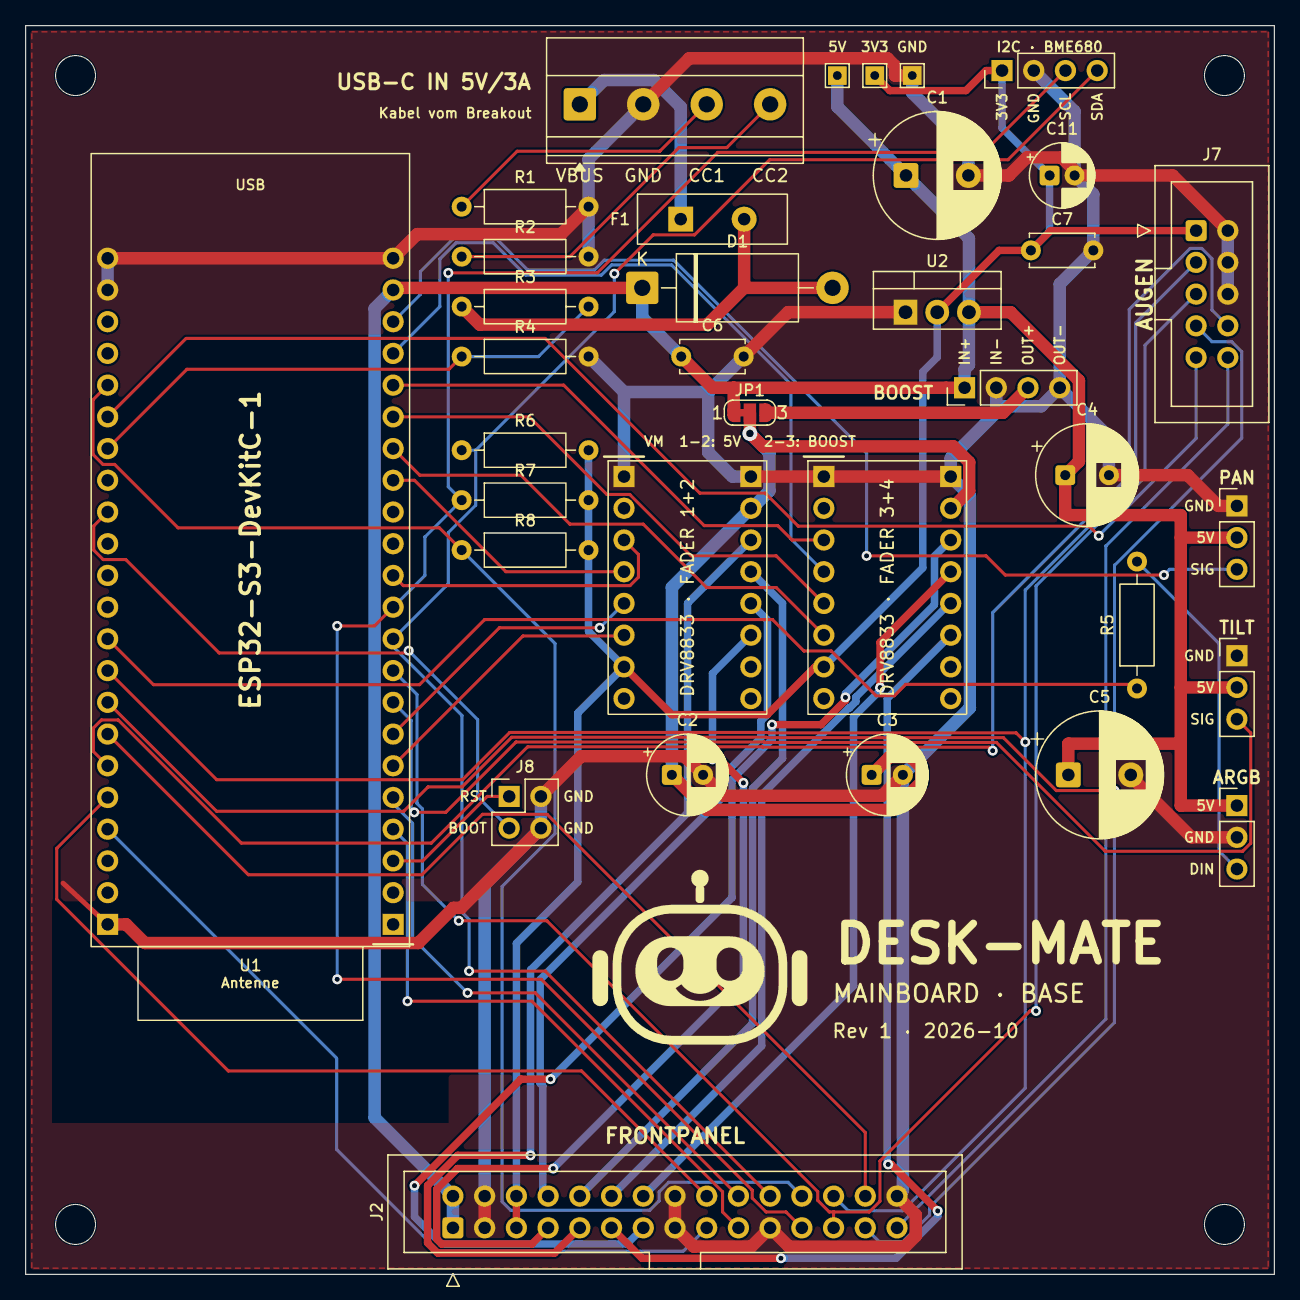
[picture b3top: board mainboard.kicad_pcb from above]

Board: 2 copper layers, 100.0 x 100.0 mm, 39 parts (0 on the bottom side), 46 nets.

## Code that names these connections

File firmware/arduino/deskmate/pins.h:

// Desk-Mate — verifizierte Pin-Map (2026-08-23; GPIO45 gestrichen 2026-10-04). Quellen: vault/Hardware/Pin-Map.md, Spec §2.3.
// Board: ESP32-S3-DevKitC-1 (WROOM-1-N16R8). Aenderungen nur mit Spec-Update.
#pragma once

// Fader (Schleifer zwingend ADC1 = GPIO1-10; ADC2 ist mit WiFi unbrauchbar)
constexpr int PIN_FADER1_WIPER = 1;   // ADC1_CH0, RC-Filter auf Frontpanel
constexpr int PIN_FADER2_WIPER = 2;   // ADC1_CH1
constexpr int PIN_FADER3_WIPER = 4;   // ADC1_CH3, Reserve (DNP)
constexpr int PIN_FADER4_WIPER = 5;   // ADC1_CH4, Reserve (DNP)
constexpr int PIN_FADER1_PWM = 6;     // LEDC 20 kHz -> DRV8833 A-IN1
constexpr int PIN_FADER1_DIR = 7;     // GPIO -> DRV8833 A-IN2
constexpr int PIN_FADER2_PWM = 8;     // LEDC -> DRV8833 B-IN1
constexpr int PIN_FADER2_DIR = 9;     // GPIO -> DRV8833 B-IN2
constexpr int PIN_FADER3_PWM = 10;    // Reserve
constexpr int PIN_FADER3_DIR = 11;    // Reserve
constexpr int PIN_FADER4_PWM = 12;    // Reserve
constexpr int PIN_FADER4_DIR = 13;    // Reserve

// Kopf
constexpr int PIN_SERVO_PAN = 14;     // LEDC 50 Hz
constexpr int PIN_SERVO_TILT = 15;    // LEDC 50 Hz
constexpr int PIN_WS2812_DATA = 38;   // RMT, Mund/Ampel; DevKit v1.1: Onboard-LED spiegelt Pixel 0 (gewollt)

// Displays (ein SPI-Bus, drei Panels)
constexpr int PIN_SPI_MOSI = 16;
constexpr int PIN_SPI_SCK = 39;       // JTAG-Default; frei, da USB-Serial-JTAG (eFuse-Default)
constexpr int PIN_SPI_DC = 40;
constexpr int PIN_CS_BELLY = 41;
constexpr int PIN_CS_EYE_L = 42;
constexpr int PIN_CS_EYE_R = 47;
// Backlight on/off und DISP_RST aller drei Displays laufen ueber den MCP23017 (GPB6 / GPB5), kein S3-Pin.

// I2C (MCP23017 0x20, MPR121 0x5A, BME680 0x76/0x77)
constexpr int PIN_I2C_SDA = 17;
constexpr int PIN_I2C_SCL = 18;
constexpr int PIN_IO_INT = 21;        // MCP23017-INT + MPR121-IRQ, wired-OR (Open-Drain, Pull-up)

// Versorgung
constexpr int PIN_PSU_SENSE = 48;     // Teiler an J1-VBUS (vor der SB540); DevKit v1.0: Onboard-LED haengt hier (unkritisch)

// Tabu: 0, 3, 45, 46 (Strapping; 45 = VDD_SPI), 19/20 (USB), 26-34 (Flash), 35-37 (Octal-PSRAM, unverbunden lassen), 43/44 (UART0/CP2102N)
